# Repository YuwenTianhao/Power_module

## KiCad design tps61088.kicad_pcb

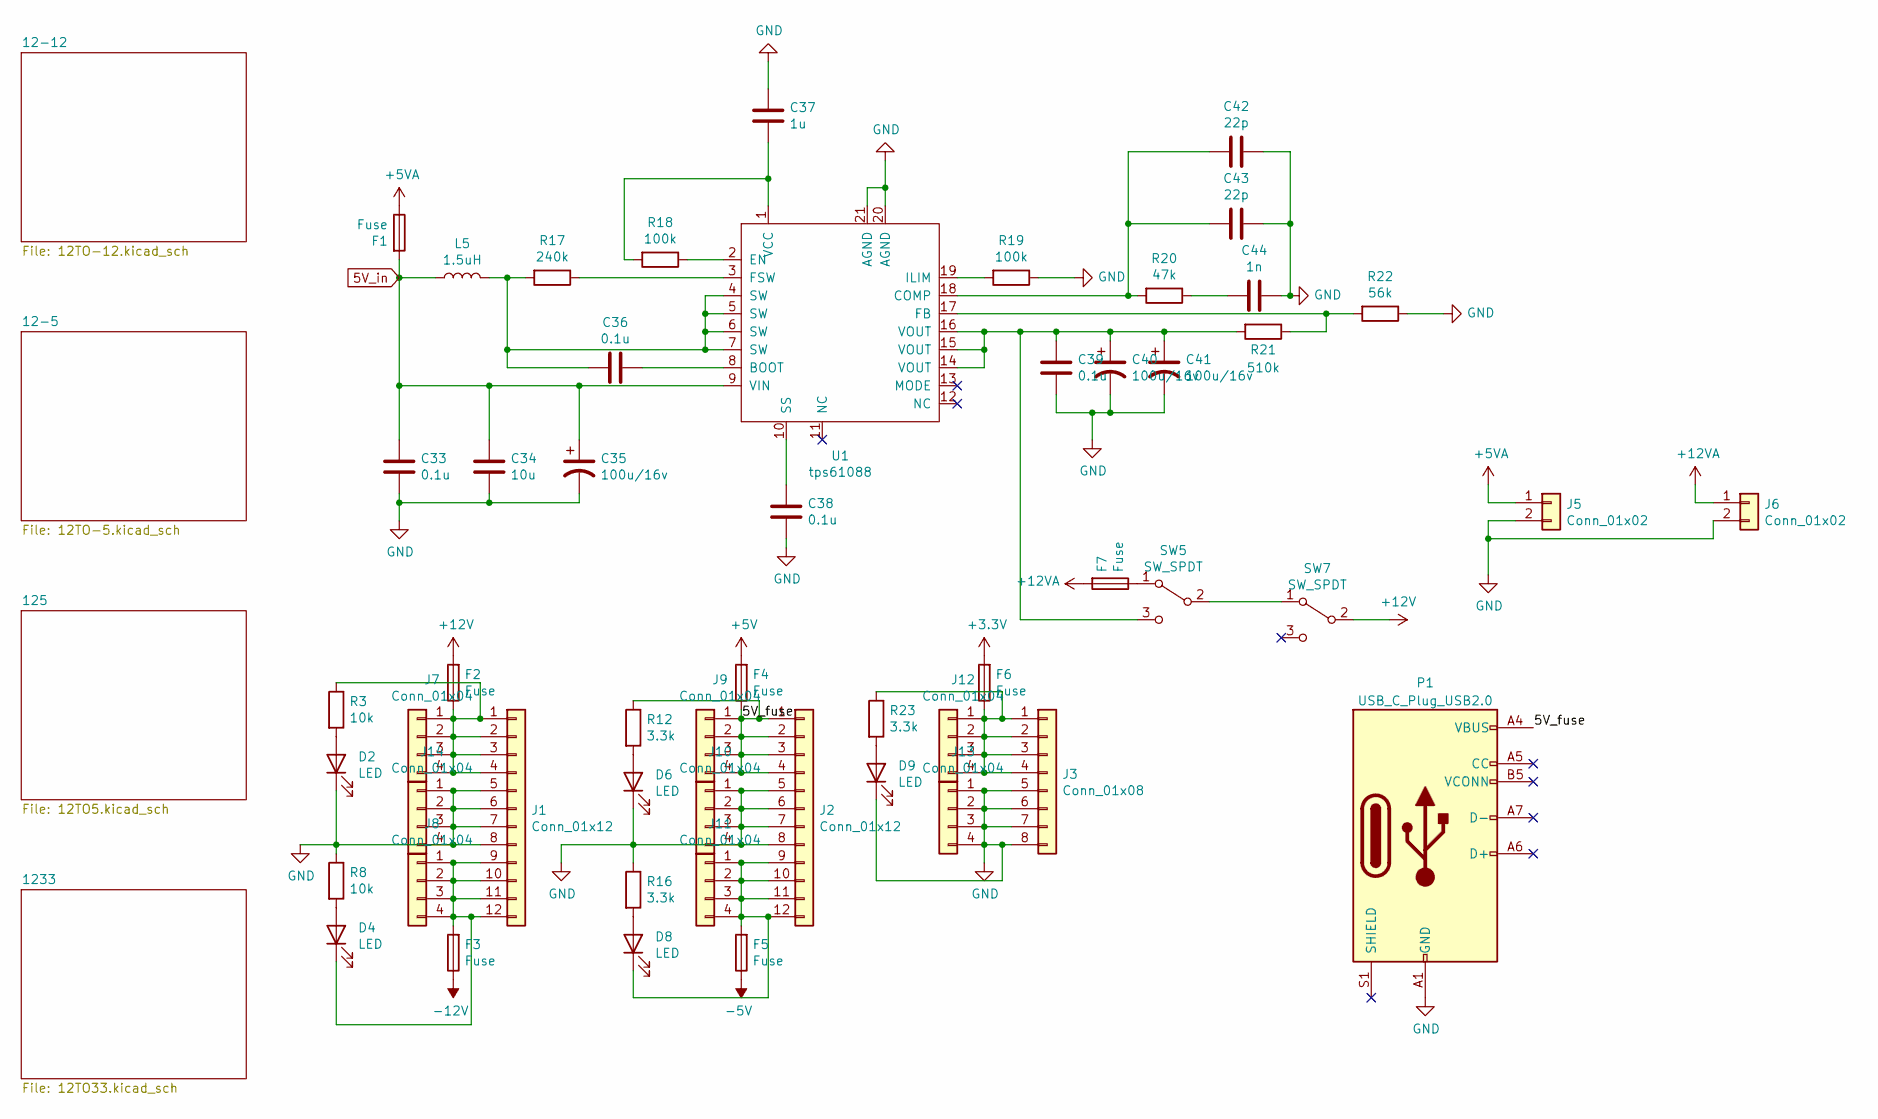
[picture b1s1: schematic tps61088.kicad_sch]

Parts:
C33, C36, C38, C39: 0.1u; C_0402_1005Metric
C34: 10u; C_0603_1608Metric
C35, C40, C41: 100u/16v; CP_Radial_D5.0mm_P2.00mm
C37: 1u; C_0402_1005Metric
C42, C43: 22p; C_0402_1005Metric
C44: 1n; C_0402_1005Metric
D2, D4, D6, D8, D9: LED; LED_1206_3216Metric
F1, F2, F3, F4, F5, F6, F7: Fuse; Fuse_1206_3216Metric
J1, J2: Conn_01x12; PhoenixContact_MSTBA_2,5_12-G-5,08_1x12_P5.08mm_Horizontal
J3: Conn_01x08; PhoenixContact_MSTBA_2,5_8-G-5,08_1x08_P5.08mm_Horizontal
J5, J6: Conn_01x02; PhoenixContact_MSTBA_2,5_2-G-5,08_1x02_P5.08mm_Horizontal
J7, J8, J9, J10, J11, J12, J13, J14: Conn_01x04; PinHeader_1x04_P2.54mm_Vertical
L5: 1.5uH; L_7.3x7.3_H3.5
P1: USB_C_Plug_USB2.0; USB_C_Receptacle_GCT_USB4105-xx-A_16P_TopMnt_Horizontal
R3, R8: 10k; R_1206_3216Metric
R12, R16, R23: 3.3k; R_1206_3216Metric
R17: 240k; R_0603_1608Metric
R18, R19: 100k; R_0402_1005Metric
R20: 47k; R_0402_1005Metric
R21: 510k; R_0402_1005Metric
R22: 56k; R_0402_1005Metric
SW5, SW7: SW_SPDT; SW_Slide_1P2T_CK_OS102011MS2Q
U1: tps61088; Texas_VQFN-RHL-20

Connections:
5V_in: C33.1, C34.1, C35.1, F1.2, L5.1, U1.9 (VIN); also elsewhere on the board
+3V3: F6.2; also elsewhere on the board
+5V: F4.2; also elsewhere on the board
+5VA: F1.1, J5.1
+12V: F2.2, SW7.2 (B); also elsewhere on the board
+12VA: F7.2, J6.1
-5V: F5.1; also elsewhere on the board
-12V: F3.1; also elsewhere on the board
/5V_fuse: F4.1, J2.1, J2.2, J2.3, J2.4, J9.1, J9.2, J9.3, J9.4, P1.A4 (VBUS), P1.A9 (VBUS), P1.B4 (VBUS), P1.B9 (VBUS), R12.1
GND: C33.2, C34.2, C35.2, C37.1, C38.2, C39.2, C40.2, C41.2, C42.1, C43.1, C44.1, D2.1 (K), D6.1 (K), D9.1 (K), J1.5, J1.6, J1.7, J1.8, J2.5, J2.6, J2.7, J2.8, J3.5, J3.6, J3.7, J3.8, J5.2, J6.2, J10.1, J10.2, J10.3, J10.4, J13.1, J13.2, J13.3, J13.4, J14.1, J14.2, J14.3, J14.4, P1.A1 (GND), P1.A12 (GND), P1.B1 (GND), P1.B12 (GND), R8.1, R16.1, R19.1, R22.1, U1.20 (AGND), U1.21 (AGND); also elsewhere on the board
unnamed: C36.2, L5.2, R17.2, U1.4 (SW), U1.5 (SW), U1.6 (SW), U1.7 (SW)
unnamed: C44.2, R20.1
unnamed: D2.2 (A), R3.2
unnamed: D4.2 (A), R8.2
unnamed 16: D4.1 (K), F3.2, J1.9, J1.10, J1.11, J1.12, J8.1, J8.2, J8.3, J8.4; also elsewhere on the board
unnamed: D6.2 (A), R12.2
unnamed: D8.2 (A), R16.2
unnamed: D8.1 (K), F5.2, J2.9, J2.10, J2.11, J2.12, J11.1, J11.2, J11.3, J11.4
unnamed: D9.2 (A), R23.2
unnamed 23: F2.1, J1.1, J1.2, J1.3, J1.4, J7.1, J7.2, J7.3, J7.4, R3.1; also elsewhere on the board
unnamed: F6.1, J3.1, J3.2, J3.3, J3.4, J12.1, J12.2, J12.3, J12.4, R23.1
unnamed: F7.1, SW5.1 (A)
unnamed 34: SW5.2 (B), SW7.1 (A); also elsewhere on the board
unnamed: C39.1, C40.1, C41.1, R21.2, SW5.3 (C), U1.14 (VOUT), U1.15 (VOUT), U1.16 (VOUT)
unnamed: C36.1, U1.8 (BOOT)
unnamed: C42.2, C43.2, R20.2, U1.18 (COMP)
unnamed: R18.1, U1.2 (EN)
unnamed: R21.1, R22.2, U1.17 (FB)
unnamed: R17.1, U1.3 (FSW)
unnamed: R19.2, U1.19 (ILIM)
unnamed: C38.1, U1.10 (SS)
unnamed: C37.2, R18.2, U1.1 (VCC)

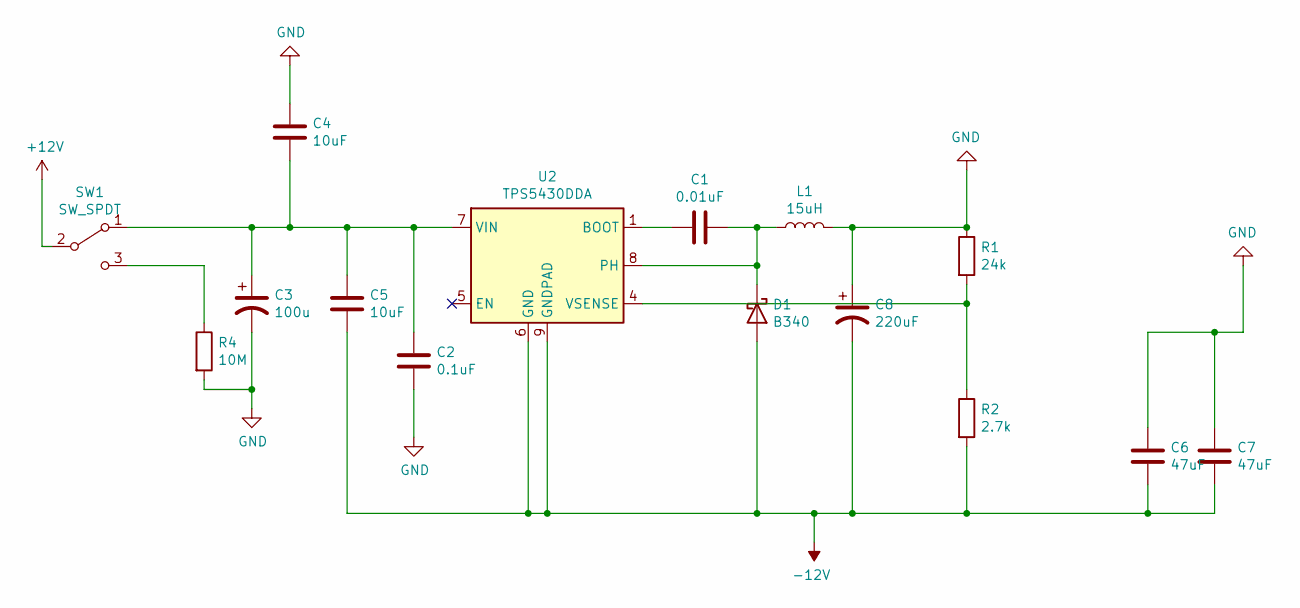
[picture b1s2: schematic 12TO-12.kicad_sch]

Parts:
C1: 0.01uF; C_0402_1005Metric
C2: 0.1uF; C_0402_1005Metric
C3: 100u; CP_Radial_D5.0mm_P2.00mm
C4, C5: 10uF; C_0603_1608Metric
C6, C7: 47uF; C_1206_3216Metric
C8: 220uF; CP_Radial_D6.3mm_P2.50mm
D1: B340; D_SMA
L1: 15uH; L_7.3x7.3_H3.5
R1: 24k; R_0402_1005Metric
R2: 2.7k; R_0603_1608Metric
R4: 10M; R_0402_1005Metric
SW1: SW_SPDT; SW_Slide_1P2T_CK_OS102011MS2Q
U2: TPS5430DDA; TI_SO-PowerPAD-8_ThermalVias

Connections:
+12V: SW1.2 (B); also elsewhere on the board
-12V: C5.2, C6.2, C7.2, C8.2, D1.2 (A), R2.2, U2.6 (GND), U2.9 (GNDPAD); also elsewhere on the board
GND: C2.2, C3.2, C4.1, C6.1, C7.1, C8.1, L1.2, R1.1, R4.2; also elsewhere on the board
unnamed: C1.2, D1.1 (K), L1.1, U2.8 (PH)
unnamed: C2.1, C3.1, C4.2, C5.1, SW1.1 (A), U2.7 (VIN)
unnamed: R4.1, SW1.3 (C)
unnamed: C1.1, U2.1 (BOOT)
unnamed: R1.2, R2.1, U2.4 (VSENSE)

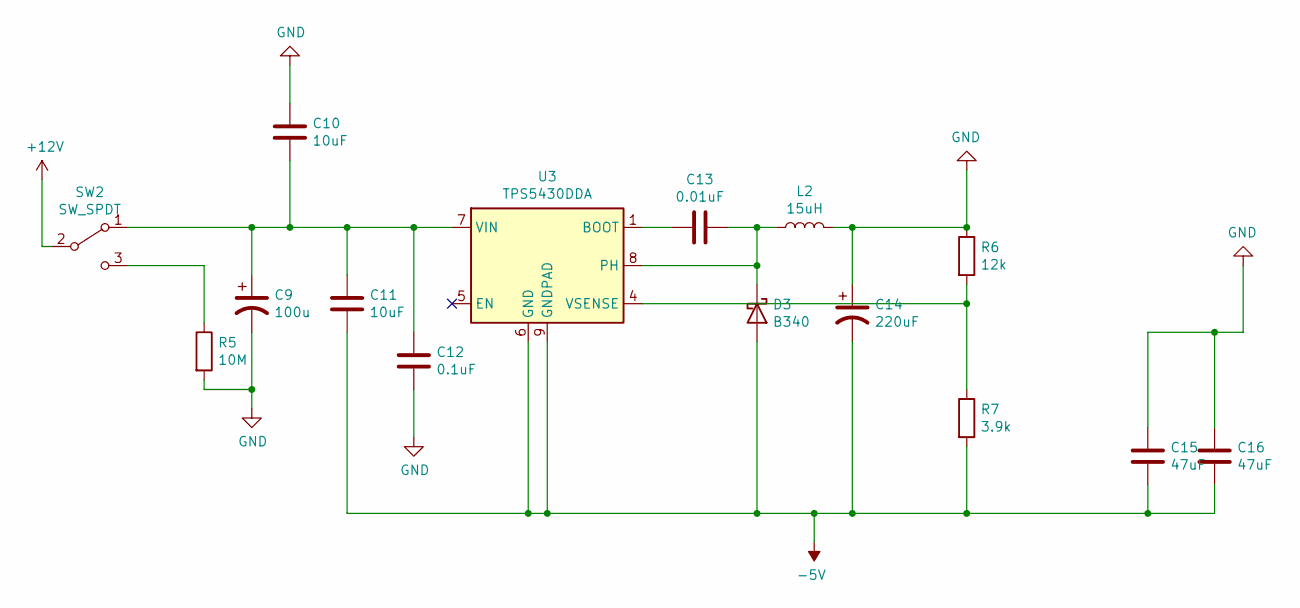
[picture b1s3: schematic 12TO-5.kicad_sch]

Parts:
C9: 100u; CP_Radial_D5.0mm_P2.00mm
C10, C11: 10uF; C_0603_1608Metric
C12: 0.1uF; C_0402_1005Metric
C13: 0.01uF; C_0402_1005Metric
C14: 220uF; CP_Radial_D6.3mm_P2.50mm
C15, C16: 47uF; C_1206_3216Metric
D3: B340; D_SMA
L2: 15uH; L_7.3x7.3_H3.5
R5: 10M; R_0402_1005Metric
R6: 12k; R_0402_1005Metric
R7: 3.9k; R_0402_1005Metric
SW2: SW_SPDT; SW_Slide_1P2T_CK_OS102011MS2Q
U3: TPS5430DDA; TI_SO-PowerPAD-8_ThermalVias

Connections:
-5V: C11.2, C14.2, C15.2, C16.2, D3.2 (A), R7.2, U3.6 (GND), U3.9 (GNDPAD); also elsewhere on the board
GND: C9.2, C10.1, C12.2, C14.1, C15.1, C16.1, L2.2, R5.2, R6.1; also elsewhere on the board
unnamed: C13.2, D3.1 (K), L2.1, U3.8 (PH)
unnamed 27: C9.1, C10.2, C11.1, C12.1, SW2.1 (A), U3.7 (VIN); also elsewhere on the board
unnamed 28: R5.1, SW2.3 (C); also elsewhere on the board
unnamed: C13.1, U3.1 (BOOT)
unnamed: R6.2, R7.1, U3.4 (VSENSE)

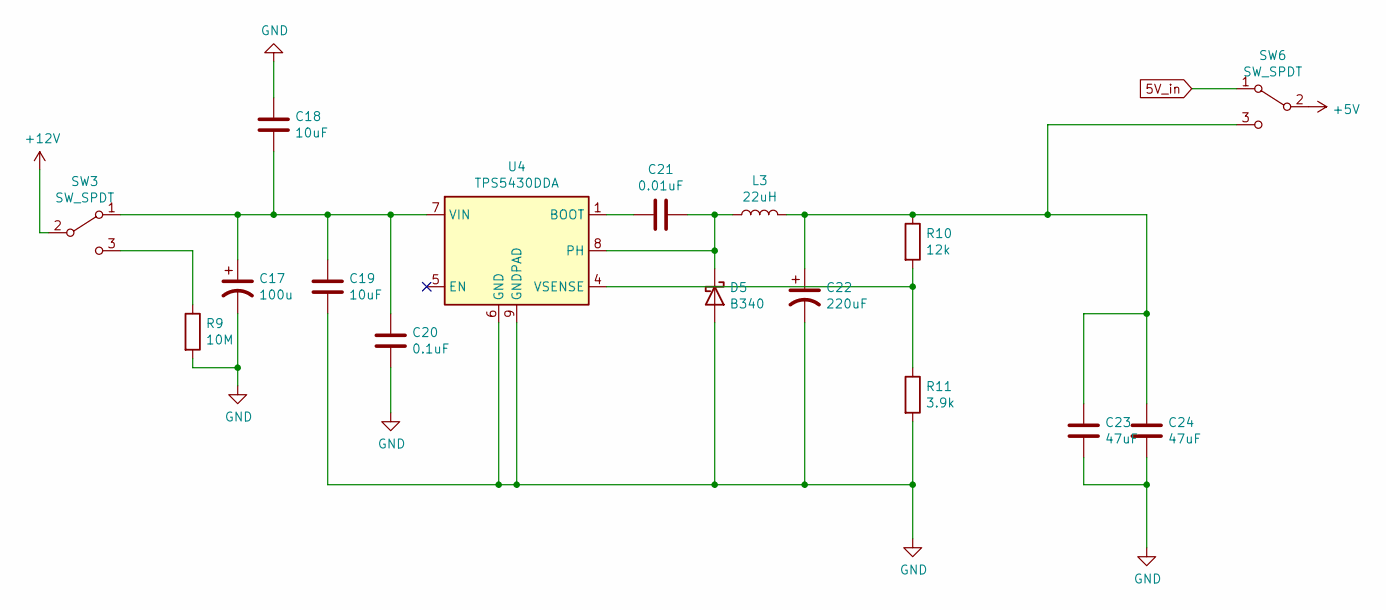
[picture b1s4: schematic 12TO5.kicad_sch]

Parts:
C17: 100u; CP_Radial_D5.0mm_P2.00mm
C18, C19: 10uF; C_0603_1608Metric
C20: 0.1uF; C_0402_1005Metric
C21: 0.01uF; C_0402_1005Metric
C22: 220uF; CP_Radial_D6.3mm_P2.50mm
C23, C24: 47uF; C_1206_3216Metric
D5: B340; D_SMA
L3: 22uH; L_7.3x7.3_H3.5
R9: 10M; R_0402_1005Metric
R10: 12k; R_0402_1005Metric
R11: 3.9k; R_0402_1005Metric
SW3, SW6: SW_SPDT; SW_Slide_1P2T_CK_OS102011MS2Q
U4: TPS5430DDA; TI_SO-PowerPAD-8_ThermalVias

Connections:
5V_in: SW6.1 (A); also elsewhere on the board
+5V: SW6.2 (B); also elsewhere on the board
GND: C17.2, C18.1, C19.2, C20.2, C22.2, C23.2, C24.2, D5.2 (A), R9.2, R11.2, U4.6 (GND), U4.9 (GNDPAD); also elsewhere on the board
unnamed: C21.2, D5.1 (K), L3.1, U4.8 (PH)
unnamed 29: C17.1, C18.2, C19.1, C20.1, SW3.1 (A), U4.7 (VIN); also elsewhere on the board
unnamed 30: R9.1, SW3.3 (C); also elsewhere on the board
unnamed: C22.1, C23.1, C24.1, L3.2, R10.1, SW6.3 (C)
unnamed: C21.1, U4.1 (BOOT)
unnamed: R10.2, R11.1, U4.4 (VSENSE)

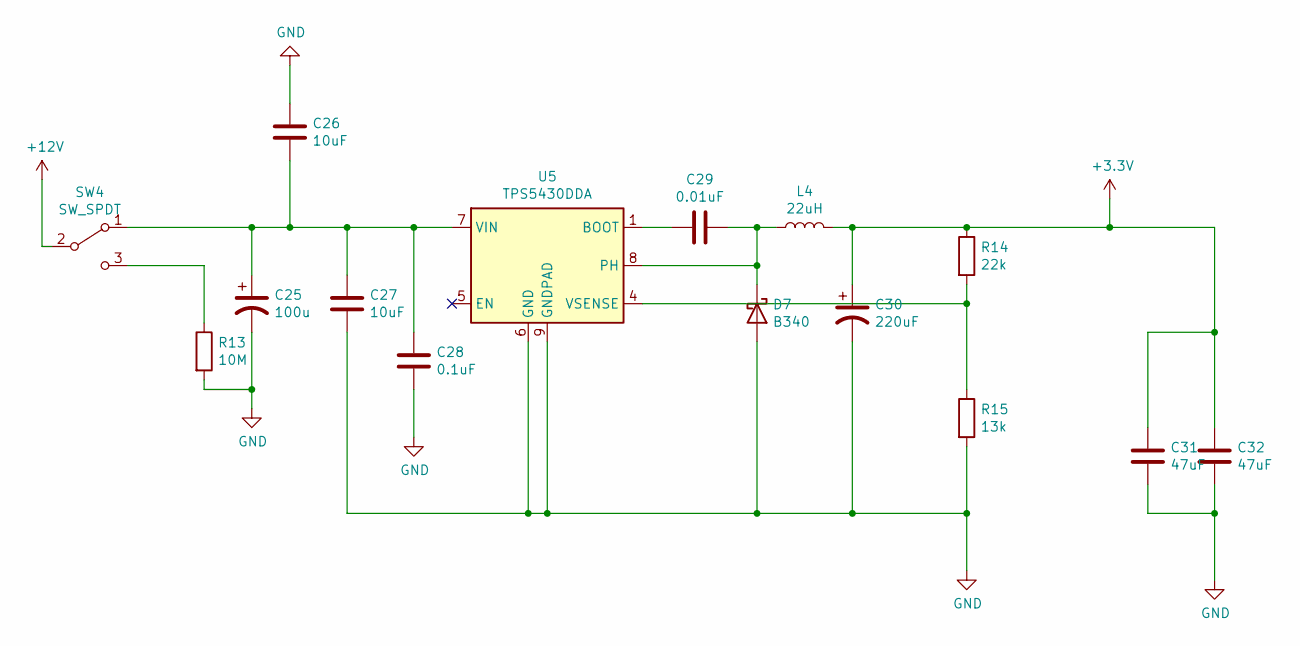
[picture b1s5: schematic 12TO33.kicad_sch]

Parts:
C25: 100u; CP_Radial_D5.0mm_P2.00mm
C26, C27: 10uF; C_0603_1608Metric
C28: 0.1uF; C_0402_1005Metric
C29: 0.01uF; C_0402_1005Metric
C30: 220uF; CP_Radial_D6.3mm_P2.50mm
C31, C32: 47uF; C_1206_3216Metric
D7: B340; D_SMA
L4: 22uH; L_7.3x7.3_H3.5
R13: 10M; R_0402_1005Metric
R14: 22k; R_0402_1005Metric
R15: 13k; R_0603_1608Metric
SW4: SW_SPDT; SW_Slide_1P2T_CK_OS102011MS2Q
U5: TPS5430DDA; TI_SO-PowerPAD-8_ThermalVias

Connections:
+3V3: C30.1, C31.1, C32.1, L4.2, R14.1; also elsewhere on the board
+12V: SW4.2 (B); also elsewhere on the board
GND: C25.2, C26.1, C27.2, C28.2, C30.2, C31.2, C32.2, D7.2 (A), R13.2, R15.2, U5.6 (GND), U5.9 (GNDPAD); also elsewhere on the board
unnamed: C29.2, D7.1 (K), L4.1, U5.8 (PH)
unnamed: C25.1, C26.2, C27.1, C28.1, SW4.1 (A), U5.7 (VIN)
unnamed: R13.1, SW4.3 (C)
unnamed: C29.1, U5.1 (BOOT)
unnamed: R14.2, R15.1, U5.4 (VSENSE)

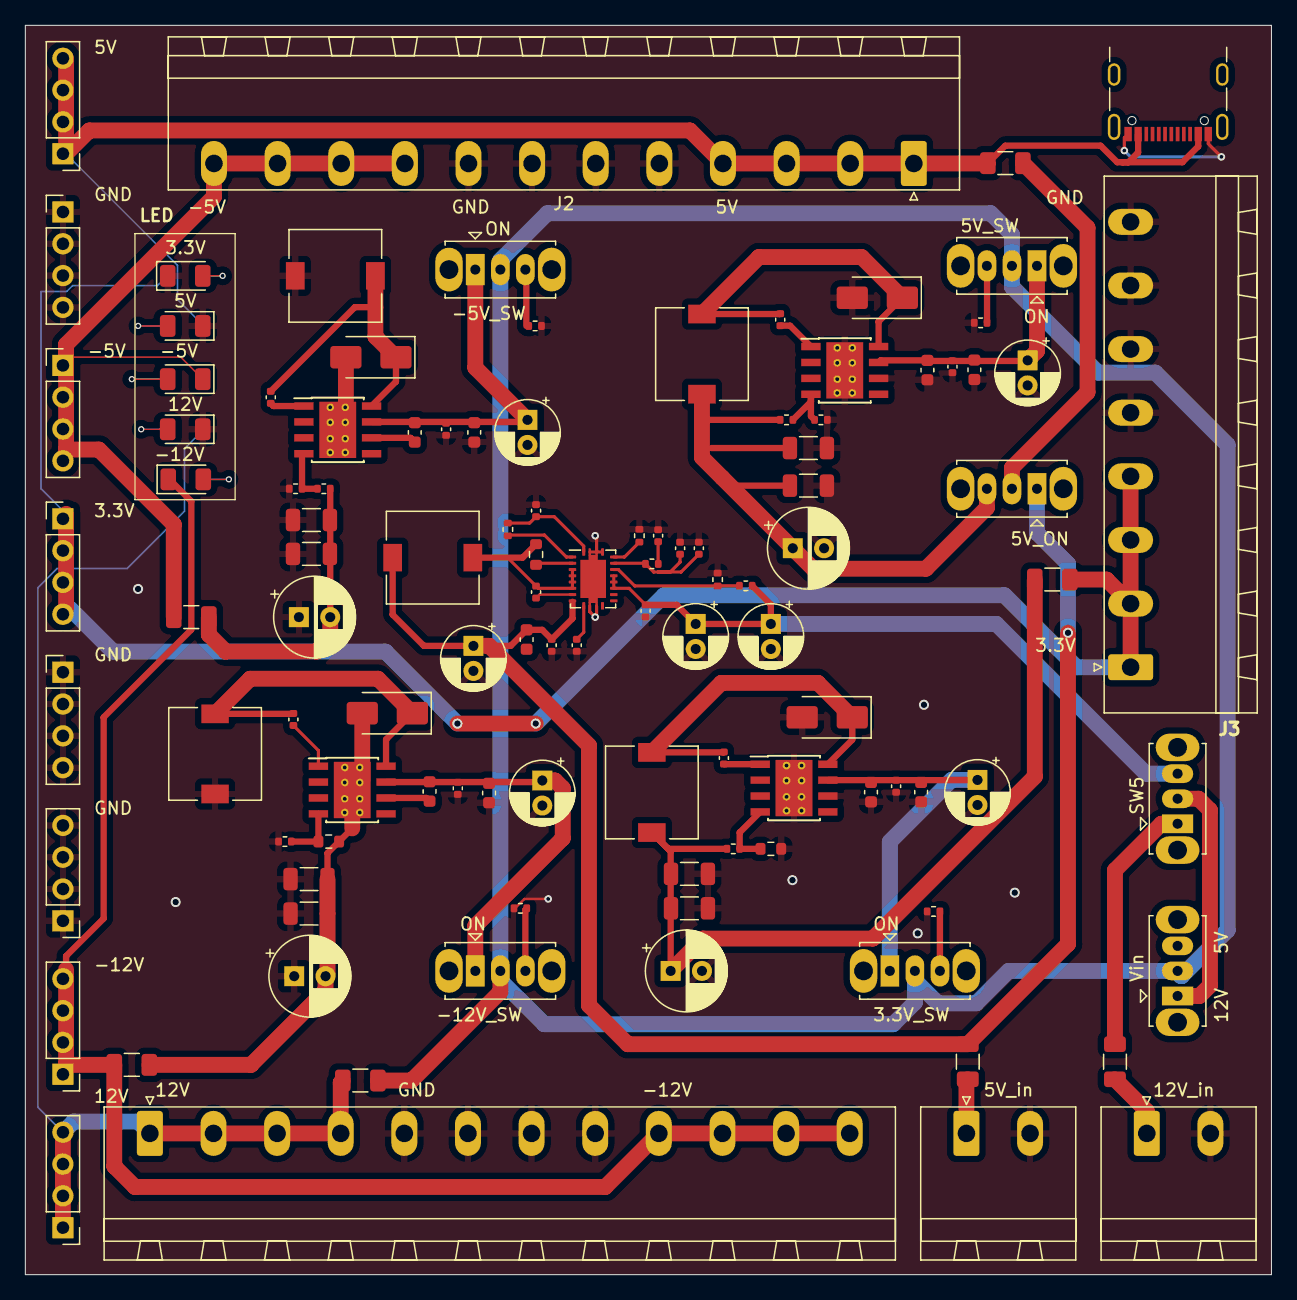
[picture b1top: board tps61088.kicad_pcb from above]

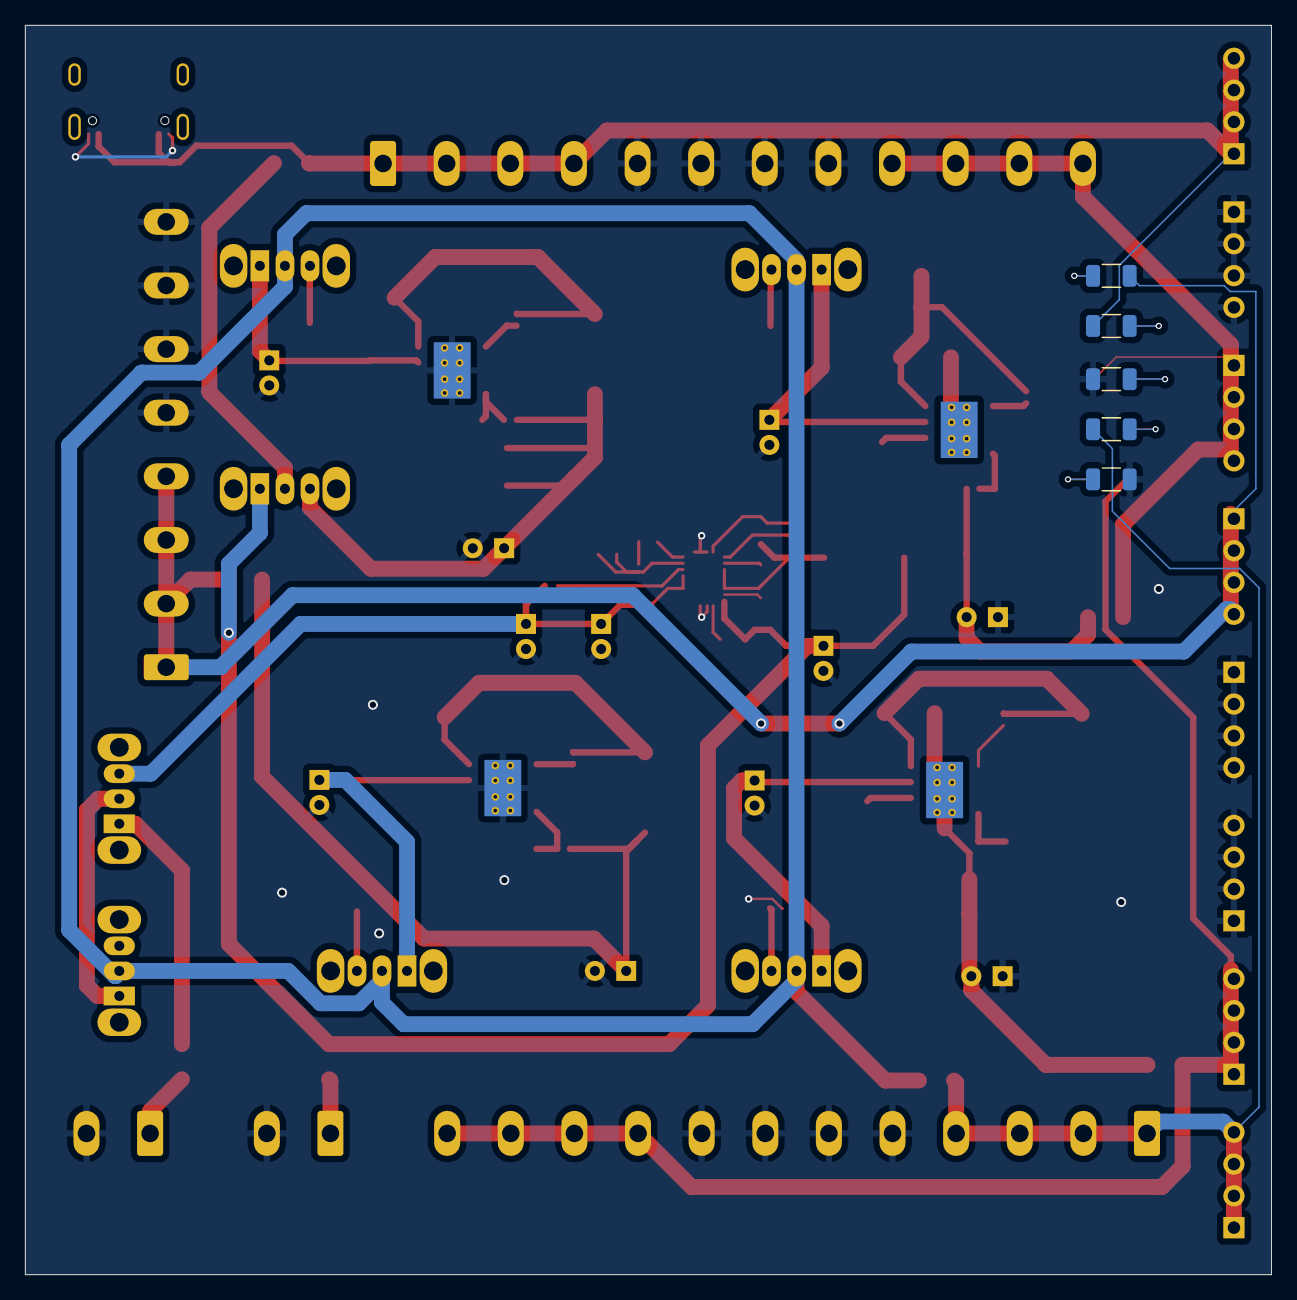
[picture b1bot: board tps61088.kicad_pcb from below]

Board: 2 copper layers, 99.5 x 99.8 mm, 114 parts (5 on the bottom side), 53 nets.

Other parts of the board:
5V_SW: SW_SPDT; SW_Slide_1P2T_CK_OS102011MS2Q
12V: Conn_01x12; PhoenixContact_MSTBA_2,5_12-G-5,08_1x12_P5.08mm_Horizontal
-5V_SW: SW_SPDT; SW_Slide_1P2T_CK_OS102011MS2Q
Vin: SW_SPDT; SW_Slide_1P2T_CK_OS102011MS2Q

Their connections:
+12V: 5V_SW.2 (B), -5V_SW.2 (B), Vin.2 (B); also elsewhere on the board
GND: 12V.5, 12V.6, 12V.7, 12V.8; also elsewhere on the board
unnamed 16: 12V.9, 12V.10, 12V.11, 12V.12; also elsewhere on the board
unnamed 23: 12V.1, 12V.2, 12V.3, 12V.4; also elsewhere on the board
unnamed 27: -5V_SW.1 (A); also elsewhere on the board
unnamed 28: -5V_SW.3 (C); also elsewhere on the board
unnamed 29: 5V_SW.1 (A); also elsewhere on the board
unnamed 30: 5V_SW.3 (C); also elsewhere on the board
unnamed 34: Vin.1 (A); also elsewhere on the board

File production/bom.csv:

Designator,Footprint,Quantity,Value,LCSC Part #
"-5V_SW, 5V_SW, SW1, SW4, SW5, SW6, Vin",SW_Slide_1P2T_CK_OS102011MS2Q,7,SW_SPDT,
"12V, J2","PhoenixContact_MSTBA_2,5_12-G-5,08_1x12_P5.08mm_Horizontal",2,Conn_01x12,
"C1, C13, C21, C29",0402,4,0.01uF,
"C10, C11, C18, C19, C26, C27, C4, C5",0603,8,10uF,
"C12, C2, C20, C28",0402,4,0.1uF,
"C14, C22, C30, C8",CP_Radial_D6.3mm_P2.50mm,4,220uF,
"C15, C16, C23, C24, C31, C32, C6, C7",1206,8,47uF,
"C17, C25, C3, C9",CP_Radial_D5.0mm_P2.00mm,4,100u,
"C33, C36, C38, C39",0402,4,0.1u,
C34,0603,1,10u,
"C35, C40, C41",CP_Radial_D5.0mm_P2.00mm,3,100u/16v,
C37,0402,1,1u,
"C42, C43",0402,2,22p,
C44,0402,1,1n,
"D1, D3, D5, D7",D_SMA,4,B340,
D2,1206,1,12V,
D4,1206,1,-12V,
D6,1206,1,5V,
D8,1206,1,-5V,
D9,1206,1,LED,
"F1, F2, F3, F4, F5, F6, F7",1206,7,Fuse,
"J10, J11, J12, J13, J14, J7, J8, J9",PinHeader_1x04_P2.54mm_Vertical,8,Conn_01x04,
J3,"PhoenixContact_MSTBA_2,5_8-G-5,08_1x08_P5.08mm_Horizontal",1,Conn_01x08,
"J5, J6","PhoenixContact_MSTBA_2,5_2-G-5,08_1x02_P5.08mm_Horizontal",2,Conn_01x02,
"L1, L2",L_7.3x7.3_H3.5,2,15uH,
"L3, L4",L_7.3x7.3_H3.5,2,22uH,
L5,L_7.3x7.3_H3.5,1,1.5uH,
P1,USB_C_Receptacle_GCT_USB4105-xx-A_16P_TopMnt_Horizontal,1,USB_C_Plug_USB2.0,
R1,0402,1,24k,
"R10, R6",0402,2,12k,
"R11, R7",0402,2,3.9k,
"R12, R16, R23",1206,3,3.3k,
"R13, R4, R5, R9",0402,4,10M,
R14,0402,1,22k,
R15,0603,1,13k,
R17,0603,1,240k,
"R18, R19",0402,2,100k,
R2,0603,1,2.7k,
R20,0402,1,47k,
R21,0402,1,510k,
R22,0402,1,56k,
"R3, R8",1206,2,10k,
U1,Texas_VQFN-RHL-20,1,tps61088,
"U2, U3, U4, U5",TI_SO-PowerPAD-8_ThermalVias,4,TPS5430DDA,

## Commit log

2023-07-05 初次绘板/未让导员检查
2023-07-05 提交前修改
2023-07-05 V1.0
    第一次下单PCB文件
